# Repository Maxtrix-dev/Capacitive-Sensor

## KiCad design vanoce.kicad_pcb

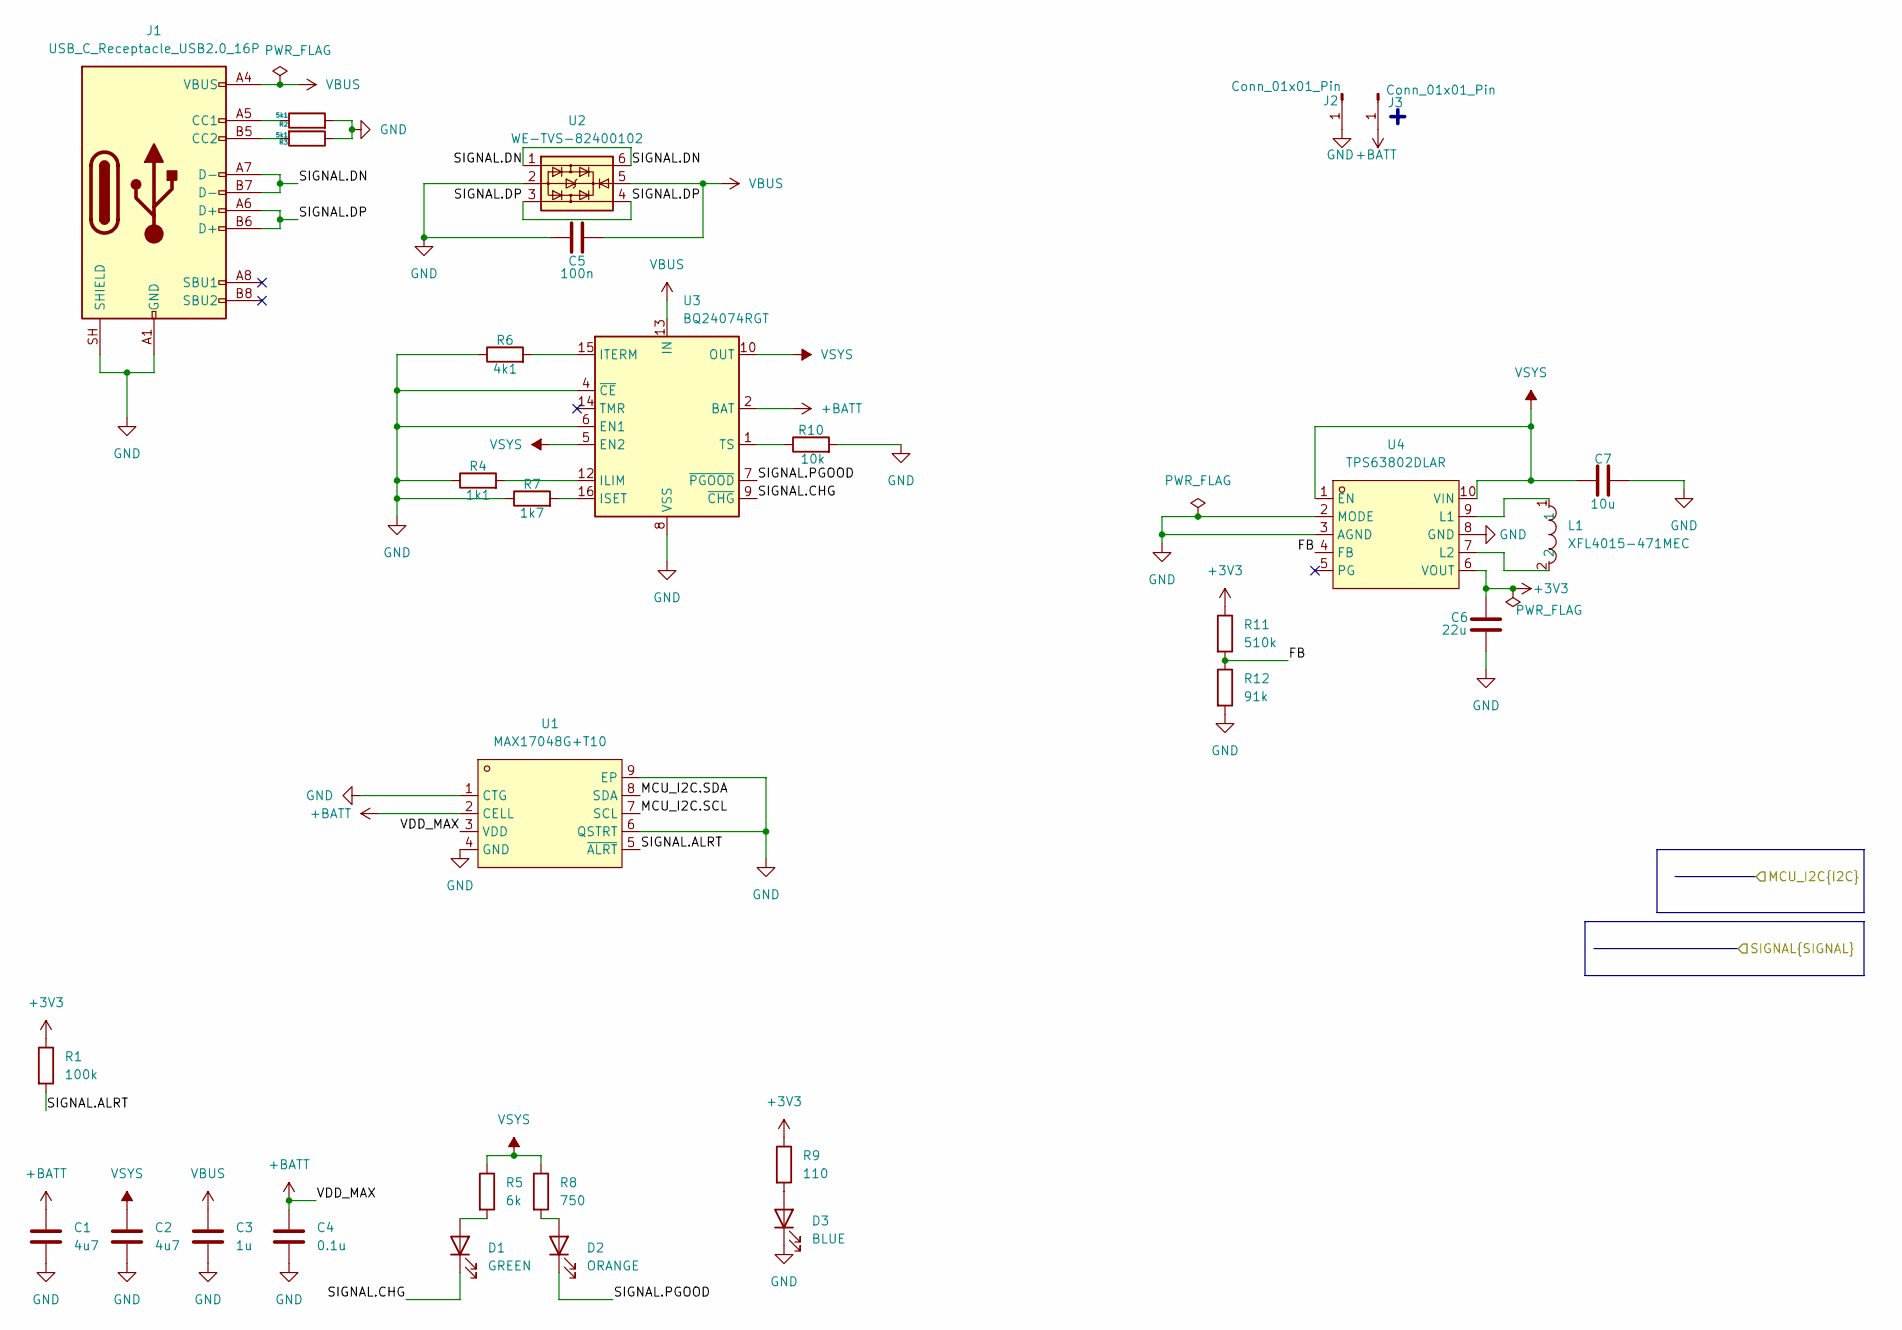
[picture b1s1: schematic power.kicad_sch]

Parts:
C1, C2: 4u7; C_0603_1608Metric_Pad1.08x0.95mm_HandSolder
C3: 1u; C_0603_1608Metric_Pad1.08x0.95mm_HandSolder
C4: 0.1u; C_0603_1608Metric_Pad1.08x0.95mm_HandSolder
C5: 100n; C_0603_1608Metric_Pad1.08x0.95mm_HandSolder
C6: 22u; C_0603_1608Metric_Pad1.08x0.95mm_HandSolder
C7: 10u; C_0603_1608Metric_Pad1.08x0.95mm_HandSolder
D1: GREEN; LED_0603_1608Metric_Pad1.05x0.95mm_HandSolder
D2: ORANGE; LED_0603_1608Metric_Pad1.05x0.95mm_HandSolder
D3: BLUE; LED_0603_1608Metric_Pad1.05x0.95mm_HandSolder
J1: USB_C_Receptacle_USB2.0_16P; USB_C_Receptacle_HRO_TYPE-C-31-M-12
J2, J3: Conn_01x01_Pin; SolderWire-0.15sqmm_1x01_D0.5mm_OD1.5mm
L1: XFL4015-471MEC; IND-SMD_L4.0-W4.0_XFL4020-102MEB; MPN XFL4015-471MEC; LCSC Part C18221164
R1: 100k; R_0603_1608Metric_Pad0.98x0.95mm_HandSolder
R2, R3: 5k1; R_0603_1608Metric_Pad0.98x0.95mm_HandSolder
R4: 1k1; R_0603_1608Metric_Pad0.98x0.95mm_HandSolder
R5: 6k; R_0603_1608Metric_Pad0.98x0.95mm_HandSolder
R6: 4k1; R_0603_1608Metric_Pad0.98x0.95mm_HandSolder
R7: 1k7; R_0603_1608Metric_Pad0.98x0.95mm_HandSolder
R8: 750; R_0603_1608Metric_Pad0.98x0.95mm_HandSolder
R9: 110; R_0603_1608Metric_Pad0.98x0.95mm_HandSolder
R10: 10k; R_0603_1608Metric_Pad0.98x0.95mm_HandSolder
R11: 510k; R_0603_1608Metric_Pad0.98x0.95mm_HandSolder
R12: 91k; R_0603_1608Metric_Pad0.98x0.95mm_HandSolder
U1: MAX17048G+T10; TDFN-8_L2.0-W2.0-P0.50-BL-EP1.2; MPN MAX17048G+T10; LCSC Part C2682616
U2: WE-TVS-82400102; SOT-23-6
U3: BQ24074RGT; VQFN-16-1EP_3x3mm_P0.5mm_EP1.6x1.6mm
U4: TPS63802DLAR; VSON-10_L3.0-W2.0-P0.50-TL; MPN TPS63802DLAR; LCSC Part C2845237

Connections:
+3V3: C6.1, R1.1, R9.1, R11.1, U4.6 (VOUT); also elsewhere on the board
+BATT: C1.1, C4.1, J3.1 (Pin_1_1), U1.2 (CELL), U1.3 (VDD), U3.2 (BAT), U3.3 (BAT)
/LED_1/MCU_I2C.SCL: U1.7 (SCL); also elsewhere on the board
/LED_1/MCU_I2C.SDA: U1.8 (SDA); also elsewhere on the board
/MCU/SIGNAL.ALRT: R1.2, U1.5 (~ALRT); also elsewhere on the board
/MCU/SIGNAL.CHG: D1.1 (K), U3.9 (~CHG); also elsewhere on the board
/MCU/SIGNAL.DN: J1.A7 (D-), J1.B7 (D-), U2.1, U2.6; also elsewhere on the board
/MCU/SIGNAL.DP: J1.A6 (D+), J1.B6 (D+), U2.3, U2.4; also elsewhere on the board
/MCU/SIGNAL.PGOOD: D2.1 (K), U3.7 (~PGOOD); also elsewhere on the board
/power/FB: R11.2, R12.1, U4.4 (FB)
GND: C1.2, C2.2, C3.2, C4.2, C5.1, C6.2, C7.1, D3.1 (K), J1.A1 (GND), J1.A12 (GND), J1.B1 (GND), J1.B12 (GND), J1.SH (SHIELD), J2.1 (Pin_1_1), R2.2, R3.1, R4.1, R6.1, R7.1, R10.2, R12.2, U1.1 (CTG), U1.4 (GND), U1.6 (QSTRT), U1.9 (EP), U2.2, U3.4 (~CE), U3.6 (EN1), U3.8 (VSS), U3.17 (VSS), U4.2 (MODE), U4.3 (AGND), U4.8 (GND); also elsewhere on the board
unnamed: D1.2 (A), R5.2
unnamed: D2.2 (A), R8.2
unnamed: D3.2 (A), R9.2
unnamed: J1.A5 (CC1), R2.1
unnamed: J1.B5 (CC2), R3.2
unnamed: R4.2, U3.12 (ILIM)
unnamed: R7.2, U3.16 (ISET)
unnamed: R6.2, U3.15 (ITERM)
unnamed: R10.1, U3.1 (TS)
unnamed: L1.1, U4.9 (L1)
unnamed: L1.2, U4.7 (L2)
VBUS: C3.1, C5.2, J1.A4 (VBUS), J1.A9 (VBUS), J1.B4 (VBUS), J1.B9 (VBUS), U2.5, U3.13 (IN)
VSYS: C2.1, C7.2, R5.1, R8.1, U3.5 (EN2), U3.10 (OUT), U3.11 (OUT), U4.1 (EN), U4.10 (VIN); also elsewhere on the board

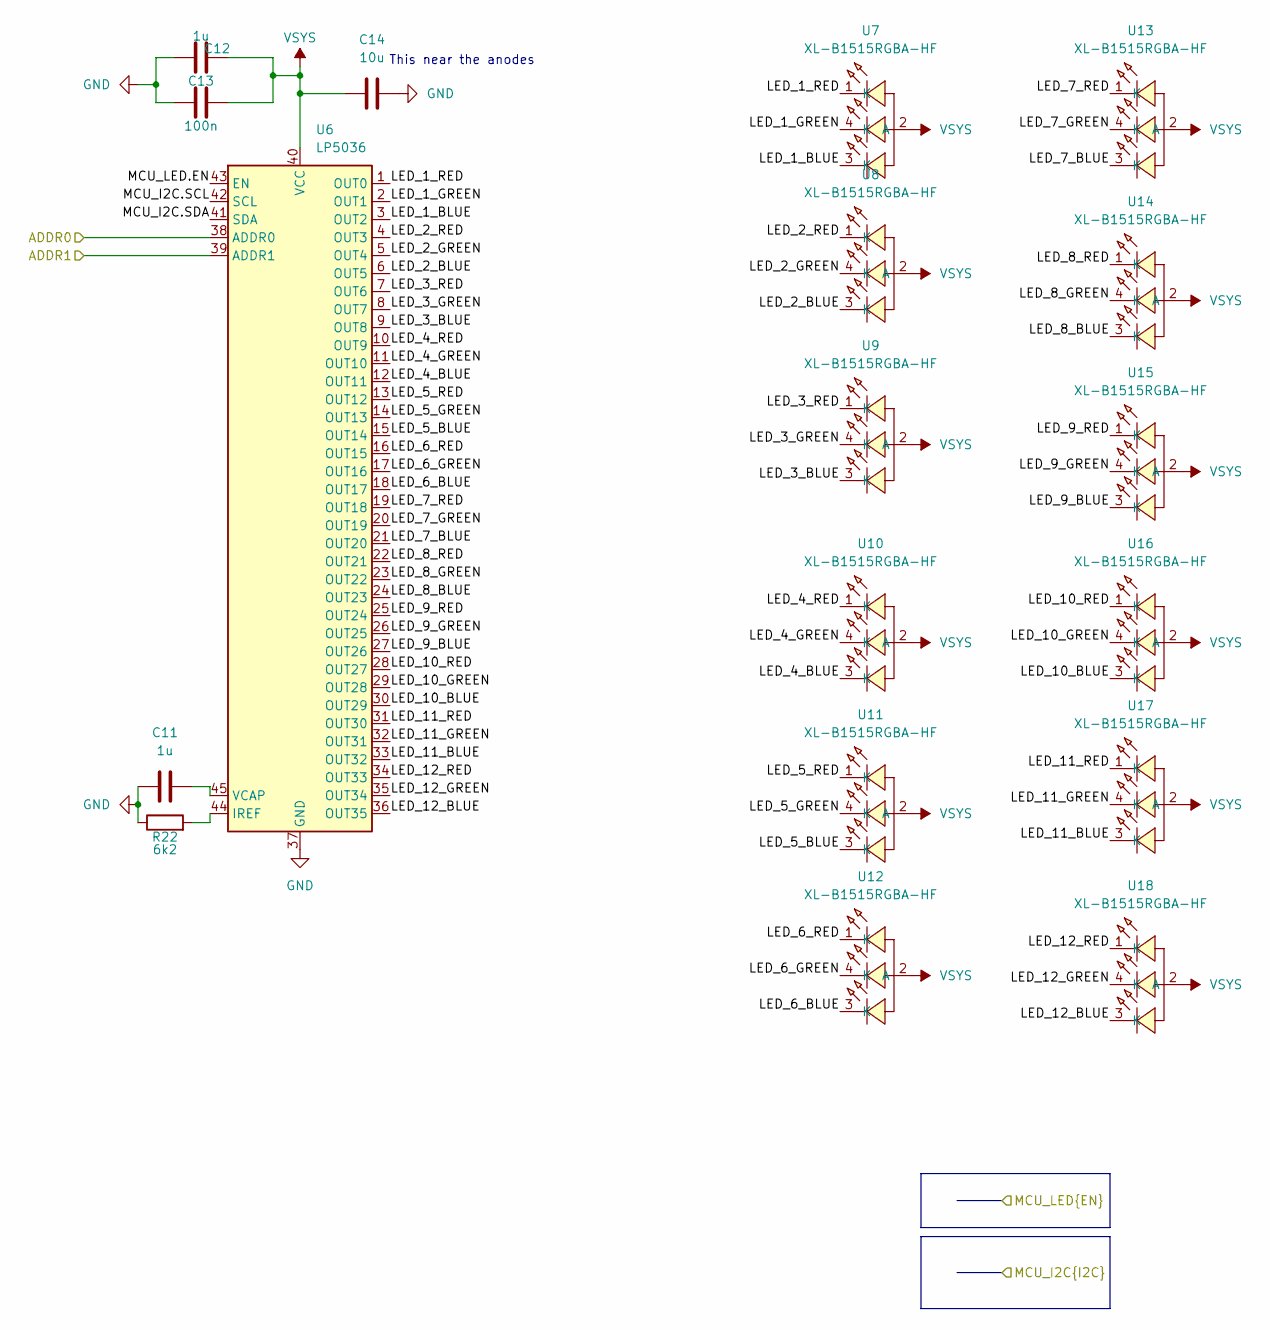
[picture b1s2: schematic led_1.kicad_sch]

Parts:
C11, C12: 1u; C_0603_1608Metric_Pad1.08x0.95mm_HandSolder
C13: 100n; C_0603_1608Metric_Pad1.08x0.95mm_HandSolder
C14: 10u; C_0603_1608Metric_Pad1.08x0.95mm_HandSolder
R22: 6k2; R_0603_1608Metric_Pad0.98x0.95mm_HandSolder
U6: LP5036; VQFN-46-1EP_5x6mm_P0.4mm_EP2.8x3.8mm
U7, U8, U9, U10, U11, U12, U13, U14, U15, U16, U17, U18: XL-B1515RGBA-HF; LED-SMD_4P-L1.6-W1.5_WHITE-LED; MPN XL-B1515RGBA-HF; LCSC Part C22461781

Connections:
/LED_1/LED_1_BLUE: U6.3 (OUT2), U7.3 (K)
/LED_1/LED_1_GREEN: U6.2 (OUT1), U7.4 (K)
/LED_1/LED_1_RED: U6.1 (OUT0), U7.1 (K)
/LED_1/LED_2_BLUE: U6.6 (OUT5), U8.3 (K)
/LED_1/LED_2_GREEN: U6.5 (OUT4), U8.4 (K)
/LED_1/LED_2_RED: U6.4 (OUT3), U8.1 (K)
/LED_1/LED_3_BLUE: U6.9 (OUT8), U9.3 (K)
/LED_1/LED_3_GREEN: U6.8 (OUT7), U9.4 (K)
/LED_1/LED_3_RED: U6.7 (OUT6), U9.1 (K)
/LED_1/LED_4_BLUE: U6.12 (OUT11), U10.3 (K)
/LED_1/LED_4_GREEN: U6.11 (OUT10), U10.4 (K)
/LED_1/LED_4_RED: U6.10 (OUT9), U10.1 (K)
/LED_1/LED_5_BLUE: U6.15 (OUT14), U11.3 (K)
/LED_1/LED_5_GREEN: U6.14 (OUT13), U11.4 (K)
/LED_1/LED_5_RED: U6.13 (OUT12), U11.1 (K)
/LED_1/LED_6_BLUE: U6.18 (OUT17), U12.3 (K)
/LED_1/LED_6_GREEN: U6.17 (OUT16), U12.4 (K)
/LED_1/LED_6_RED: U6.16 (OUT15), U12.1 (K)
/LED_1/LED_7_BLUE: U6.21 (OUT20), U13.3 (K)
/LED_1/LED_7_GREEN: U6.20 (OUT19), U13.4 (K)
/LED_1/LED_7_RED: U6.19 (OUT18), U13.1 (K)
/LED_1/LED_8_BLUE: U6.24 (OUT23), U14.3 (K)
/LED_1/LED_8_GREEN: U6.23 (OUT22), U14.4 (K)
/LED_1/LED_8_RED: U6.22 (OUT21), U14.1 (K)
/LED_1/LED_9_BLUE: U6.27 (OUT26), U15.3 (K)
/LED_1/LED_9_GREEN: U6.26 (OUT25), U15.4 (K)
/LED_1/LED_9_RED: U6.25 (OUT24), U15.1 (K)
/LED_1/LED_10_BLUE: U6.30 (OUT29), U16.3 (K)
/LED_1/LED_10_GREEN: U6.29 (OUT28), U16.4 (K)
/LED_1/LED_10_RED: U6.28 (OUT27), U16.1 (K)
/LED_1/LED_11_BLUE: U6.33 (OUT32), U17.3 (K)
/LED_1/LED_11_GREEN: U6.32 (OUT31), U17.4 (K)
/LED_1/LED_11_RED: U6.31 (OUT30), U17.1 (K)
/LED_1/LED_12_BLUE: U6.36 (OUT35), U18.3 (K)
/LED_1/LED_12_GREEN: U6.35 (OUT34), U18.4 (K)
/LED_1/LED_12_RED: U6.34 (OUT33), U18.1 (K)
/LED_1/MCU_I2C.SCL: U6.42 (SCL); also elsewhere on the board
/LED_1/MCU_I2C.SDA: U6.41 (SDA); also elsewhere on the board
/LED_1/MCU_LED.EN: U6.43 (EN); also elsewhere on the board
GND: C11.1, C12.1, C13.2, C14.2, R22.1, U6.37 (GND), U6.38 (ADDR0), U6.39 (ADDR1), U6.46 (GND), U6.47 (GND); also elsewhere on the board
unnamed: R22.2, U6.44 (IREF)
unnamed: C11.2, U6.45 (VCAP)
VSYS: C12.2, C13.1, C14.1, U6.40 (VCC), U7.2 (A), U8.2 (A), U9.2 (A), U10.2 (A), U11.2 (A), U12.2 (A), U13.2 (A), U14.2 (A), U15.2 (A), U16.2 (A), U17.2 (A), U18.2 (A); also elsewhere on the board

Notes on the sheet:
This near the anodes

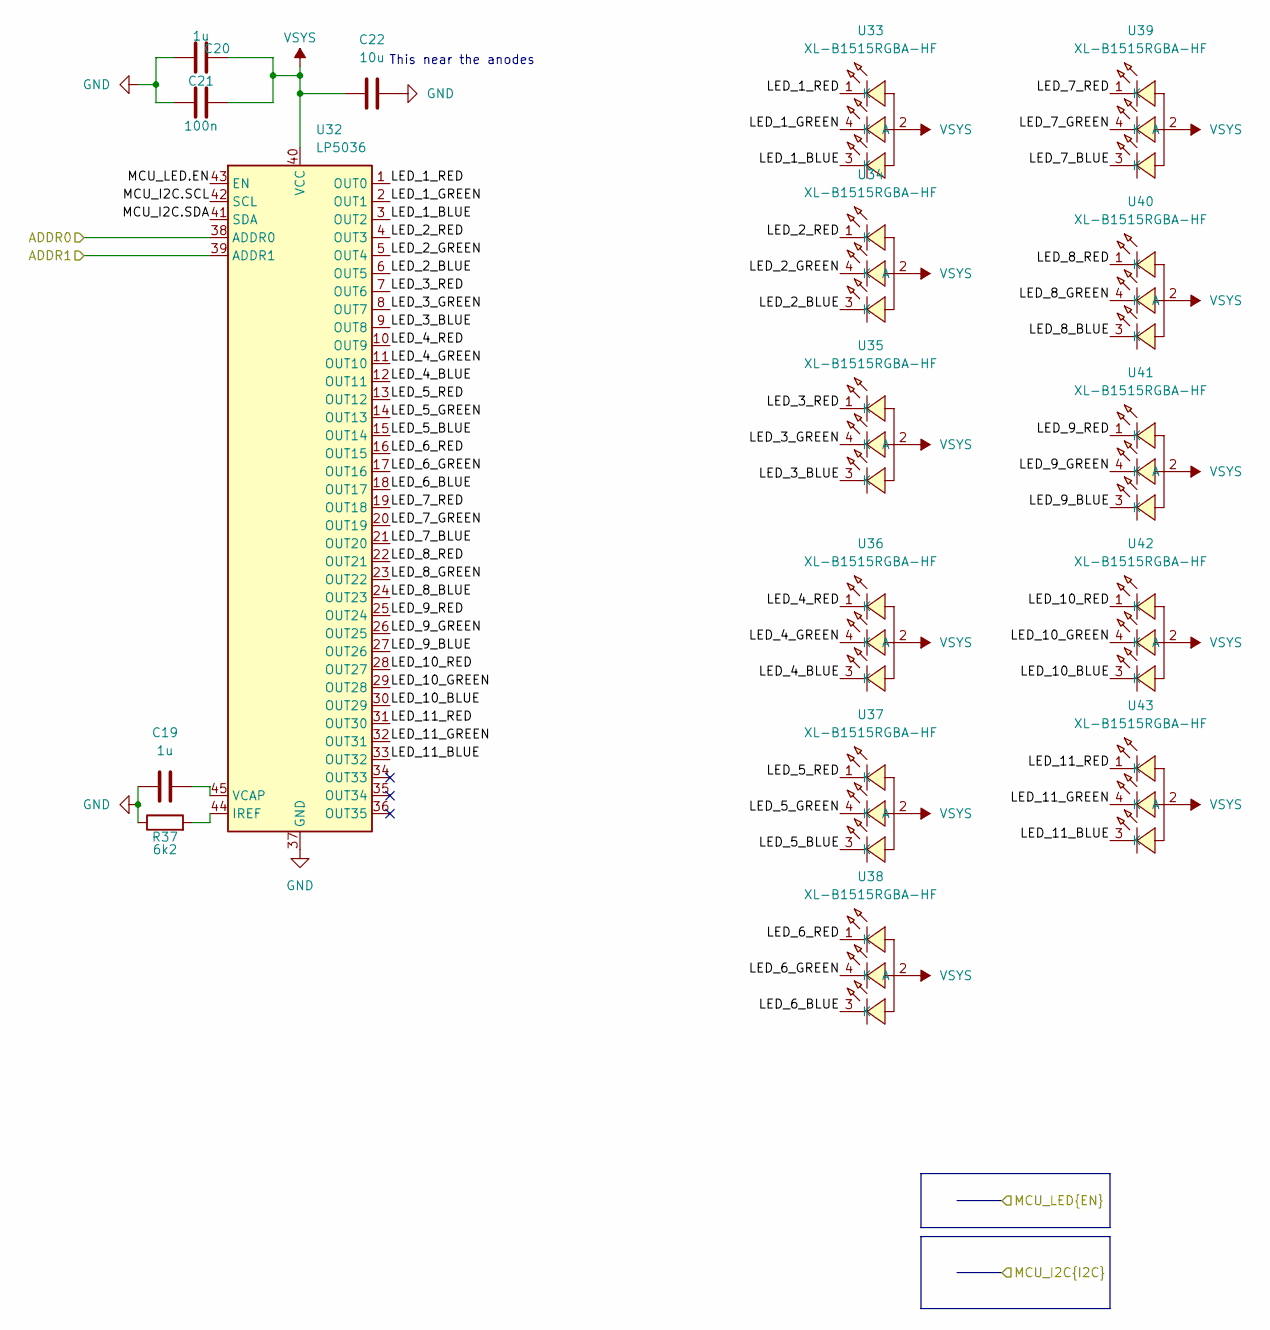
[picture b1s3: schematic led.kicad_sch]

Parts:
C19, C20: 1u; C_0603_1608Metric_Pad1.08x0.95mm_HandSolder
C21: 100n; C_0603_1608Metric_Pad1.08x0.95mm_HandSolder
C22: 10u; C_0603_1608Metric_Pad1.08x0.95mm_HandSolder
R37: 6k2; R_0603_1608Metric_Pad0.98x0.95mm_HandSolder
U32: LP5036; VQFN-46-1EP_5x6mm_P0.4mm_EP2.8x3.8mm
U33, U34, U35, U36, U37, U38, U39, U40, U41, U42, U43: XL-B1515RGBA-HF; LED-SMD_4P-L1.6-W1.5_WHITE-LED; MPN XL-B1515RGBA-HF; LCSC Part C22461781

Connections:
/LED_1/MCU_I2C.SCL: U32.42 (SCL); also elsewhere on the board
/LED_1/MCU_I2C.SDA: U32.41 (SDA); also elsewhere on the board
/LED_1/MCU_LED.EN: U32.43 (EN); also elsewhere on the board
/LED_3/LED_1_BLUE: U32.3 (OUT2), U33.3 (K)
/LED_3/LED_1_GREEN: U32.2 (OUT1), U33.4 (K)
/LED_3/LED_1_RED: U32.1 (OUT0), U33.1 (K)
/LED_3/LED_2_BLUE: U32.6 (OUT5), U34.3 (K)
/LED_3/LED_2_GREEN: U32.5 (OUT4), U34.4 (K)
/LED_3/LED_2_RED: U32.4 (OUT3), U34.1 (K)
/LED_3/LED_3_BLUE: U32.9 (OUT8), U35.3 (K)
/LED_3/LED_3_GREEN: U32.8 (OUT7), U35.4 (K)
/LED_3/LED_3_RED: U32.7 (OUT6), U35.1 (K)
/LED_3/LED_4_BLUE: U32.12 (OUT11), U36.3 (K)
/LED_3/LED_4_GREEN: U32.11 (OUT10), U36.4 (K)
/LED_3/LED_4_RED: U32.10 (OUT9), U36.1 (K)
/LED_3/LED_5_BLUE: U32.15 (OUT14), U37.3 (K)
/LED_3/LED_5_GREEN: U32.14 (OUT13), U37.4 (K)
/LED_3/LED_5_RED: U32.13 (OUT12), U37.1 (K)
/LED_3/LED_6_BLUE: U32.18 (OUT17), U38.3 (K)
/LED_3/LED_6_GREEN: U32.17 (OUT16), U38.4 (K)
/LED_3/LED_6_RED: U32.16 (OUT15), U38.1 (K)
/LED_3/LED_7_BLUE: U32.21 (OUT20), U39.3 (K)
/LED_3/LED_7_GREEN: U32.20 (OUT19), U39.4 (K)
/LED_3/LED_7_RED: U32.19 (OUT18), U39.1 (K)
/LED_3/LED_8_BLUE: U32.24 (OUT23), U40.3 (K)
/LED_3/LED_8_GREEN: U32.23 (OUT22), U40.4 (K)
/LED_3/LED_8_RED: U32.22 (OUT21), U40.1 (K)
/LED_3/LED_9_BLUE: U32.27 (OUT26), U41.3 (K)
/LED_3/LED_9_GREEN: U32.26 (OUT25), U41.4 (K)
/LED_3/LED_9_RED: U32.25 (OUT24), U41.1 (K)
/LED_3/LED_10_BLUE: U32.30 (OUT29), U42.3 (K)
/LED_3/LED_10_GREEN: U32.29 (OUT28), U42.4 (K)
/LED_3/LED_10_RED: U32.28 (OUT27), U42.1 (K)
/LED_3/LED_11_BLUE: U32.33 (OUT32), U43.3 (K)
/LED_3/LED_11_GREEN: U32.32 (OUT31), U43.4 (K)
/LED_3/LED_11_RED: U32.31 (OUT30), U43.1 (K)
GND: C19.1, C20.1, C21.2, C22.2, R37.1, U32.37 (GND), U32.39 (ADDR1), U32.46 (GND), U32.47 (GND); also elsewhere on the board
unnamed: R37.2, U32.44 (IREF)
unnamed: C19.2, U32.45 (VCAP)
VSYS: C20.2, C21.1, C22.1, U32.38 (ADDR0), U32.40 (VCC), U33.2 (A), U34.2 (A), U35.2 (A), U36.2 (A), U37.2 (A), U38.2 (A), U39.2 (A), U40.2 (A), U41.2 (A), U42.2 (A), U43.2 (A); also elsewhere on the board

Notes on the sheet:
This near the anodes

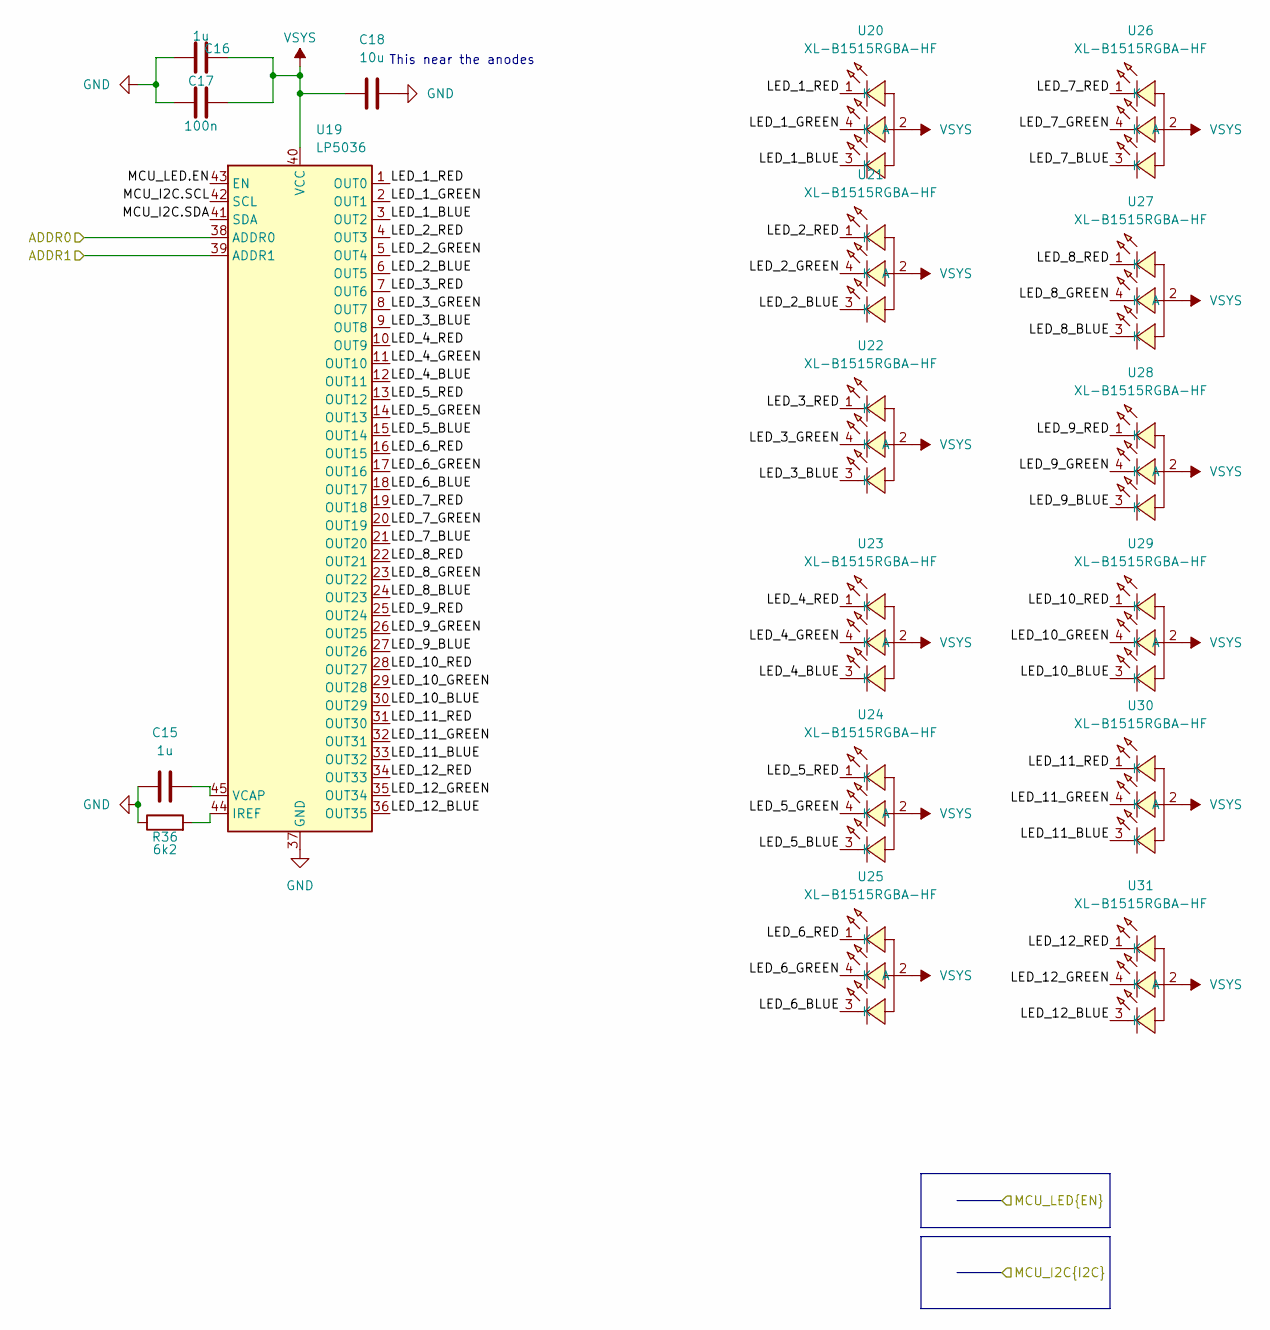
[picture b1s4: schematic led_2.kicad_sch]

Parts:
C15, C16: 1u; C_0603_1608Metric_Pad1.08x0.95mm_HandSolder
C17: 100n; C_0603_1608Metric_Pad1.08x0.95mm_HandSolder
C18: 10u; C_0603_1608Metric_Pad1.08x0.95mm_HandSolder
R36: 6k2; R_0603_1608Metric_Pad0.98x0.95mm_HandSolder
U19: LP5036; VQFN-46-1EP_5x6mm_P0.4mm_EP2.8x3.8mm
U20, U21, U22, U23, U24, U25, U26, U27, U28, U29, U30, U31: XL-B1515RGBA-HF; LED-SMD_4P-L1.6-W1.5_WHITE-LED; MPN XL-B1515RGBA-HF; LCSC Part C22461781

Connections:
/LED_1/MCU_I2C.SCL: U19.42 (SCL); also elsewhere on the board
/LED_1/MCU_I2C.SDA: U19.41 (SDA); also elsewhere on the board
/LED_1/MCU_LED.EN: U19.43 (EN); also elsewhere on the board
/LED_2/LED_1_BLUE: U19.3 (OUT2), U20.3 (K)
/LED_2/LED_1_GREEN: U19.2 (OUT1), U20.4 (K)
/LED_2/LED_1_RED: U19.1 (OUT0), U20.1 (K)
/LED_2/LED_2_BLUE: U19.6 (OUT5), U21.3 (K)
/LED_2/LED_2_GREEN: U19.5 (OUT4), U21.4 (K)
/LED_2/LED_2_RED: U19.4 (OUT3), U21.1 (K)
/LED_2/LED_3_BLUE: U19.9 (OUT8), U22.3 (K)
/LED_2/LED_3_GREEN: U19.8 (OUT7), U22.4 (K)
/LED_2/LED_3_RED: U19.7 (OUT6), U22.1 (K)
/LED_2/LED_4_BLUE: U19.12 (OUT11), U23.3 (K)
/LED_2/LED_4_GREEN: U19.11 (OUT10), U23.4 (K)
/LED_2/LED_4_RED: U19.10 (OUT9), U23.1 (K)
/LED_2/LED_5_BLUE: U19.15 (OUT14), U24.3 (K)
/LED_2/LED_5_GREEN: U19.14 (OUT13), U24.4 (K)
/LED_2/LED_5_RED: U19.13 (OUT12), U24.1 (K)
/LED_2/LED_6_BLUE: U19.18 (OUT17), U25.3 (K)
/LED_2/LED_6_GREEN: U19.17 (OUT16), U25.4 (K)
/LED_2/LED_6_RED: U19.16 (OUT15), U25.1 (K)
/LED_2/LED_7_BLUE: U19.21 (OUT20), U26.3 (K)
/LED_2/LED_7_GREEN: U19.20 (OUT19), U26.4 (K)
/LED_2/LED_7_RED: U19.19 (OUT18), U26.1 (K)
/LED_2/LED_8_BLUE: U19.24 (OUT23), U27.3 (K)
/LED_2/LED_8_GREEN: U19.23 (OUT22), U27.4 (K)
/LED_2/LED_8_RED: U19.22 (OUT21), U27.1 (K)
/LED_2/LED_9_BLUE: U19.27 (OUT26), U28.3 (K)
/LED_2/LED_9_GREEN: U19.26 (OUT25), U28.4 (K)
/LED_2/LED_9_RED: U19.25 (OUT24), U28.1 (K)
/LED_2/LED_10_BLUE: U19.30 (OUT29), U29.3 (K)
/LED_2/LED_10_GREEN: U19.29 (OUT28), U29.4 (K)
/LED_2/LED_10_RED: U19.28 (OUT27), U29.1 (K)
/LED_2/LED_11_BLUE: U19.33 (OUT32), U30.3 (K)
/LED_2/LED_11_GREEN: U19.32 (OUT31), U30.4 (K)
/LED_2/LED_11_RED: U19.31 (OUT30), U30.1 (K)
/LED_2/LED_12_BLUE: U19.36 (OUT35), U31.3 (K)
/LED_2/LED_12_GREEN: U19.35 (OUT34), U31.4 (K)
/LED_2/LED_12_RED: U19.34 (OUT33), U31.1 (K)
GND: C15.1, C16.1, C17.2, C18.2, R36.1, U19.37 (GND), U19.38 (ADDR0), U19.46 (GND), U19.47 (GND); also elsewhere on the board
unnamed: R36.2, U19.44 (IREF)
unnamed: C15.2, U19.45 (VCAP)
VSYS: C16.2, C17.1, C18.1, U19.39 (ADDR1), U19.40 (VCC), U20.2 (A), U21.2 (A), U22.2 (A), U23.2 (A), U24.2 (A), U25.2 (A), U26.2 (A), U27.2 (A), U28.2 (A), U29.2 (A), U30.2 (A), U31.2 (A); also elsewhere on the board

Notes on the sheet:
This near the anodes

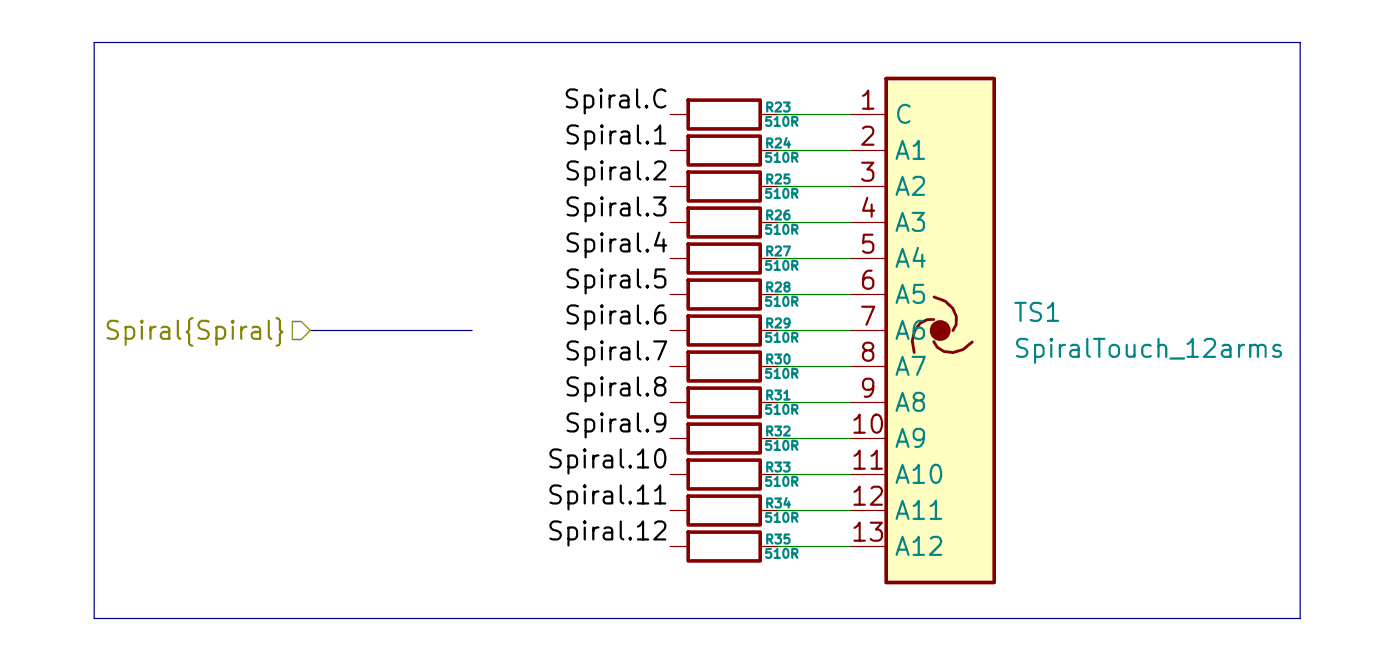
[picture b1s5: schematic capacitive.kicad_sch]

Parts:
R23, R24, R25, R26, R27, R28, R29, R30, R31, R32, R33, R34, R35: 510R; R_0603_1608Metric_Pad0.98x0.95mm_HandSolder
TS1: SpiralTouch_12arms; SpiralTouch_D30_N12_C10_T40_VO

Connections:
/Capacitive Touch/Spiral.1: R24.2; also elsewhere on the board
/Capacitive Touch/Spiral.2: R25.2; also elsewhere on the board
/Capacitive Touch/Spiral.3: R26.2; also elsewhere on the board
/Capacitive Touch/Spiral.4: R27.2; also elsewhere on the board
/Capacitive Touch/Spiral.5: R28.2; also elsewhere on the board
/Capacitive Touch/Spiral.6: R29.2; also elsewhere on the board
/Capacitive Touch/Spiral.7: R30.2; also elsewhere on the board
/Capacitive Touch/Spiral.8: R31.2; also elsewhere on the board
/Capacitive Touch/Spiral.9: R32.2; also elsewhere on the board
/Capacitive Touch/Spiral.10: R33.2; also elsewhere on the board
/Capacitive Touch/Spiral.11: R34.2; also elsewhere on the board
/Capacitive Touch/Spiral.12: R35.2; also elsewhere on the board
/Capacitive Touch/Spiral.C: R23.2; also elsewhere on the board
unnamed: R24.1, TS1.2 (A1)
unnamed: R25.1, TS1.3 (A2)
unnamed: R26.1, TS1.4 (A3)
unnamed: R27.1, TS1.5 (A4)
unnamed: R28.1, TS1.6 (A5)
unnamed: R29.1, TS1.7 (A6)
unnamed: R30.1, TS1.8 (A7)
unnamed: R31.1, TS1.9 (A8)
unnamed: R32.1, TS1.10 (A9)
unnamed: R33.1, TS1.11 (A10)
unnamed: R34.1, TS1.12 (A11)
unnamed: R35.1, TS1.13 (A12)
unnamed: R23.1, TS1.1 (C)

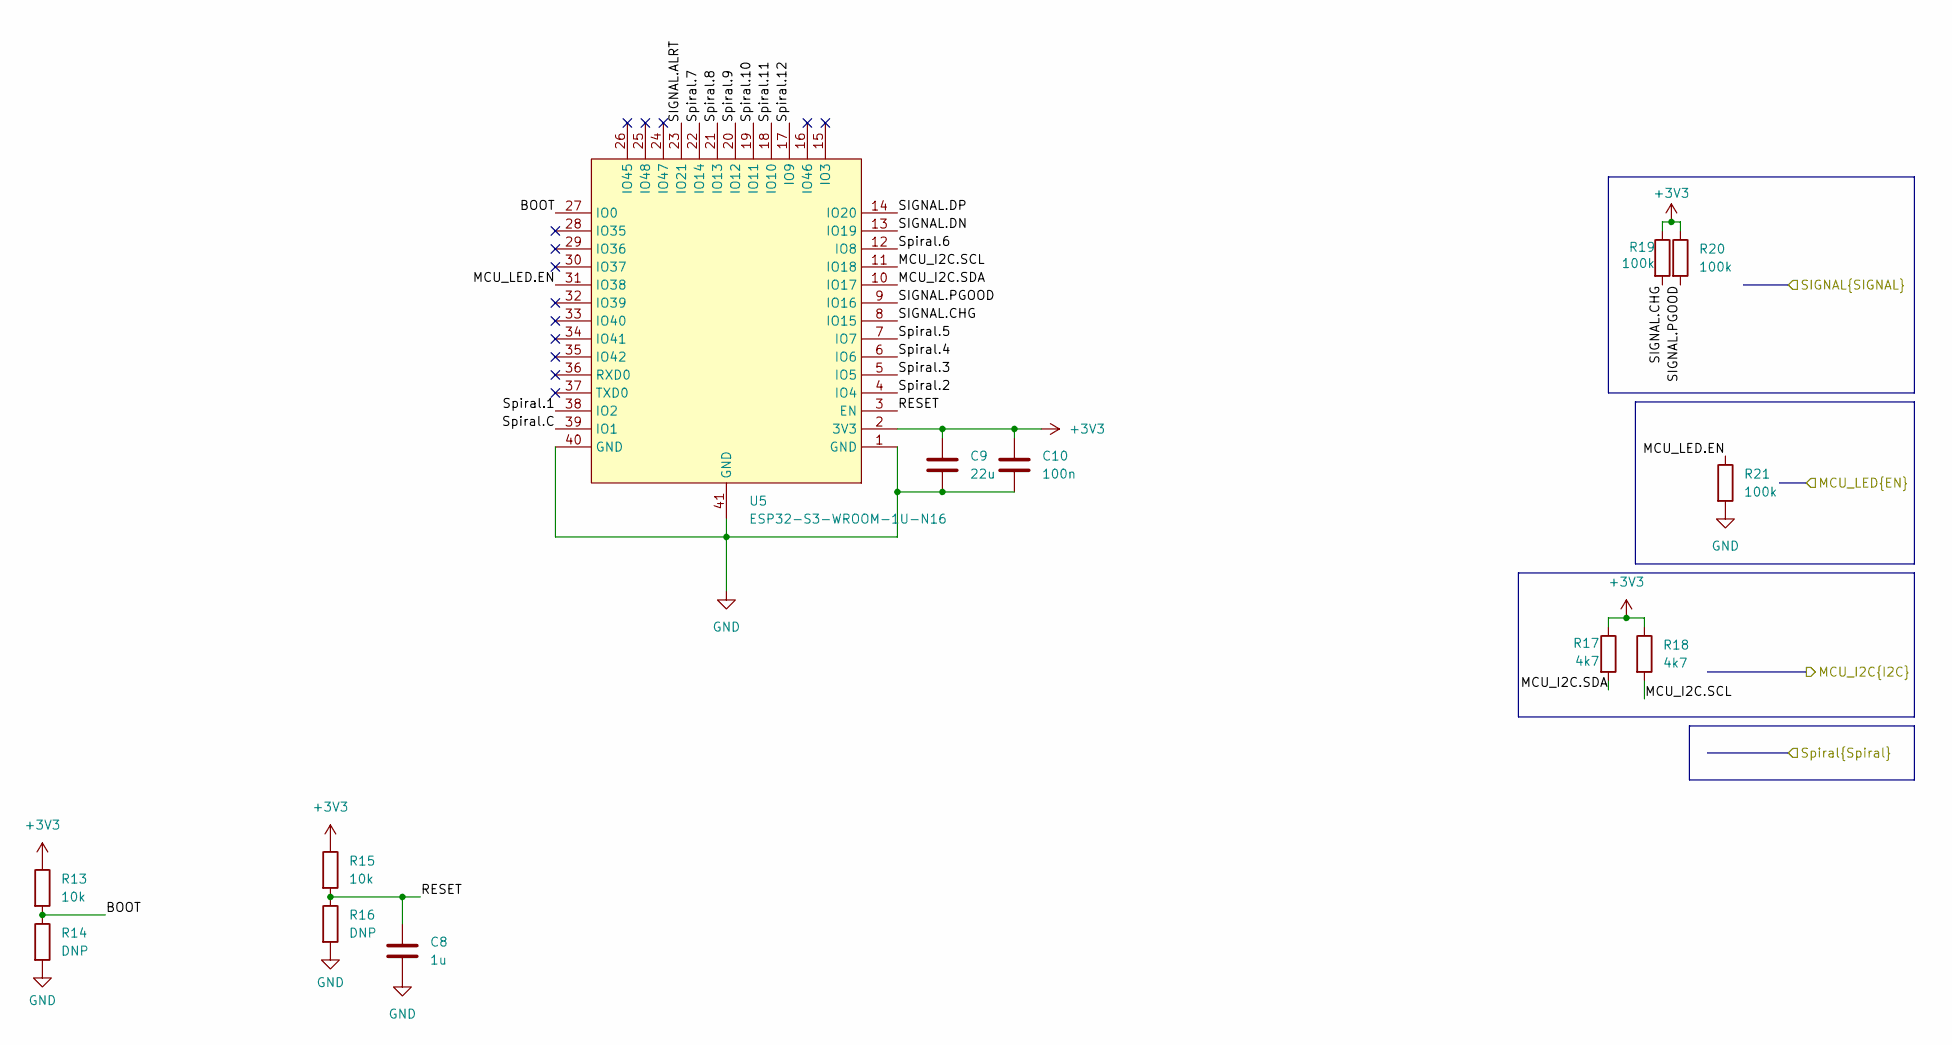
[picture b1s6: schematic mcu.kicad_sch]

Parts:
C8: 1u; C_0603_1608Metric_Pad1.08x0.95mm_HandSolder
C9: 22u; C_0603_1608Metric_Pad1.08x0.95mm_HandSolder
C10: 100n; C_0603_1608Metric_Pad1.08x0.95mm_HandSolder
R13, R15: 10k; R_0603_1608Metric_Pad0.98x0.95mm_HandSolder
R14, R16: DNP; R_0603_1608Metric_Pad0.98x0.95mm_HandSolder
R17, R18: 4k7; R_0603_1608Metric_Pad0.98x0.95mm_HandSolder
R19, R20, R21: 100k; R_0603_1608Metric_Pad0.98x0.95mm_HandSolder
U5: ESP32-S3-WROOM-1U-N16; WIRELM-SMD_ESP32-S3-WROOM-1U; MPN ESP32-S3-WROOM-1U-N16; LCSC Part C2980298

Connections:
+3V3: C9.1, C10.1, R13.1, R15.1, R17.1, R18.1, R19.1, R20.1, U5.2 (3V3); also elsewhere on the board
/Capacitive Touch/Spiral.1: U5.38 (IO2); also elsewhere on the board
/Capacitive Touch/Spiral.2: U5.4 (IO4); also elsewhere on the board
/Capacitive Touch/Spiral.3: U5.5 (IO5); also elsewhere on the board
/Capacitive Touch/Spiral.4: U5.6 (IO6); also elsewhere on the board
/Capacitive Touch/Spiral.5: U5.7 (IO7); also elsewhere on the board
/Capacitive Touch/Spiral.6: U5.12 (IO8); also elsewhere on the board
/Capacitive Touch/Spiral.7: U5.22 (IO14); also elsewhere on the board
/Capacitive Touch/Spiral.8: U5.21 (IO13); also elsewhere on the board
/Capacitive Touch/Spiral.9: U5.20 (IO12); also elsewhere on the board
/Capacitive Touch/Spiral.10: U5.19 (IO11); also elsewhere on the board
/Capacitive Touch/Spiral.11: U5.18 (IO10); also elsewhere on the board
/Capacitive Touch/Spiral.12: U5.17 (IO9); also elsewhere on the board
/Capacitive Touch/Spiral.C: U5.39 (IO1); also elsewhere on the board
/LED_1/MCU_I2C.SCL: R18.2, U5.11 (IO18); also elsewhere on the board
/LED_1/MCU_I2C.SDA: R17.2, U5.10 (IO17); also elsewhere on the board
/LED_1/MCU_LED.EN: R21.1, U5.31 (IO38); also elsewhere on the board
/MCU/BOOT: R13.2, R14.1, U5.27 (IO0)
/MCU/RESET: C8.1, R15.2, R16.1, U5.3 (EN)
/MCU/SIGNAL.ALRT: U5.23 (IO21); also elsewhere on the board
/MCU/SIGNAL.CHG: R19.2, U5.8 (IO15); also elsewhere on the board
/MCU/SIGNAL.DN: U5.13 (IO19); also elsewhere on the board
/MCU/SIGNAL.DP: U5.14 (IO20); also elsewhere on the board
/MCU/SIGNAL.PGOOD: R20.2, U5.9 (IO16); also elsewhere on the board
GND: C8.2, C9.2, C10.2, R14.2, R16.2, R21.2, U5.1 (GND), U5.40 (GND), U5.41 (GND); also elsewhere on the board
